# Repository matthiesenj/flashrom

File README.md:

# Flashrom
The main purpose of this project is to implement a flashmemory-based kickstart ROM substitute/switcher for the Commodore Amiga line of computers.
It may also serve as a general-purpose substitute for 27Cx00 compatible JEDEC pinout (EP)ROMs.

It is based around the 29F800 1MB flash memory chip and is very close to the same dimensions as a 40 pin DIP socket, and low profile.

## Disclaimer!
This is a homebrew project - I provide absolutely no warranties or promises about the suitability of this for you or your hardware - if something breaks, it's on yourself!

## Features
- 1MB flash-based programmable (EP)ROM replacement
- About the same size as a 40-pin DIP socket, so fits side by side in Amiga 4000
- Divisible into two or four ROM sections, switchable using regular toggle switch
- Pairable switching for systems using two ROMs, for example Amiga 1200 and 4000
- Slim pins to avoid damage to DIP socket wipes
- Compatibility mode for Amiga 500 rev 3-5, which have two signals swapped in the socket

## Inspiration
There are some other projects out there which are similar to this one, and while I probably can't guarantee that there was no inspirational effects at all from these, all of the electrical design, schematics and PCB layouts in this project were done completely from scratch.

## Compatibility
I've only tested this with Amiga 4000 and Amiga 500, as it's all I have access to, but as the pinout matches 27C400 there's no reason it shouldn't work in other 5V systems using this pinout.
Jumpers provide compatibility with Amiga 500 rev 3 and 5 which has two ROM socket pins swapped (other revs affected?).

## Important!
- Be careful about electrostatic discharge when handling - signals that go to an optional ROM switch have provisions for in-circuit ESD protection
- When using in a 42-pin socket (for 27C160 JEDEC pinout), make sure the board is inserted in socket positions 2-41 - do *not* insert into position 1!
- Make sure not to insert board backwards - the notch marking should match the notch of the socket

## Versatility

## Socket preservation
Dual-wipe DIP sockets will get damaged by inserting a regular pin strip with 0.6 x 0.6 mm square pins into it - or, it's actually when you need to insert a 40 pin DIP chip again, it will cause problems, because the wide pins of the pin strip bends the wipes so they don't spring back properly (a regular DIP chip has about 0.25mm wide pins).

This project is intended to use 1.27mm pin strips with every other pin removed. These can be found with 0.4 x 0.4mm (or slimmer) pins which won't damage the dual-wipe socket.
Because of this, the PCB holes for the pins are smaller to correctly align the strips while being soldered.

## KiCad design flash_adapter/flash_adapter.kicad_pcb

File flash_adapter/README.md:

# TL866CS/A flash adapter for 29Fx00 flashrom project

This PCBA makes it possible to use a TL866 programmer with the TSOP48/SOP44 adapter to program the 29Fx00 flashrom solution.
It's also useful for reading the contents of EPROMs and mask ROMs with a JEDEC pinout matching an Amiga ROM or 27Cx00 EPROM.

The design is very simple, it just reroutes the signals of the TSOP/SOP adapter to match the pinout of mentioned ROMs/EPROMs.
Only a few headers need to be soldered to the board, and the through holes for the main socket are Ø 1.0mm to be able to fit a Textool ZIF socket if so desired.
The 4-wire cable serves to connect the 4 missing signals on the 40-pin DIP interface required for programming (_WE, RY_BY, A18, and _RESET) to the programming adapter

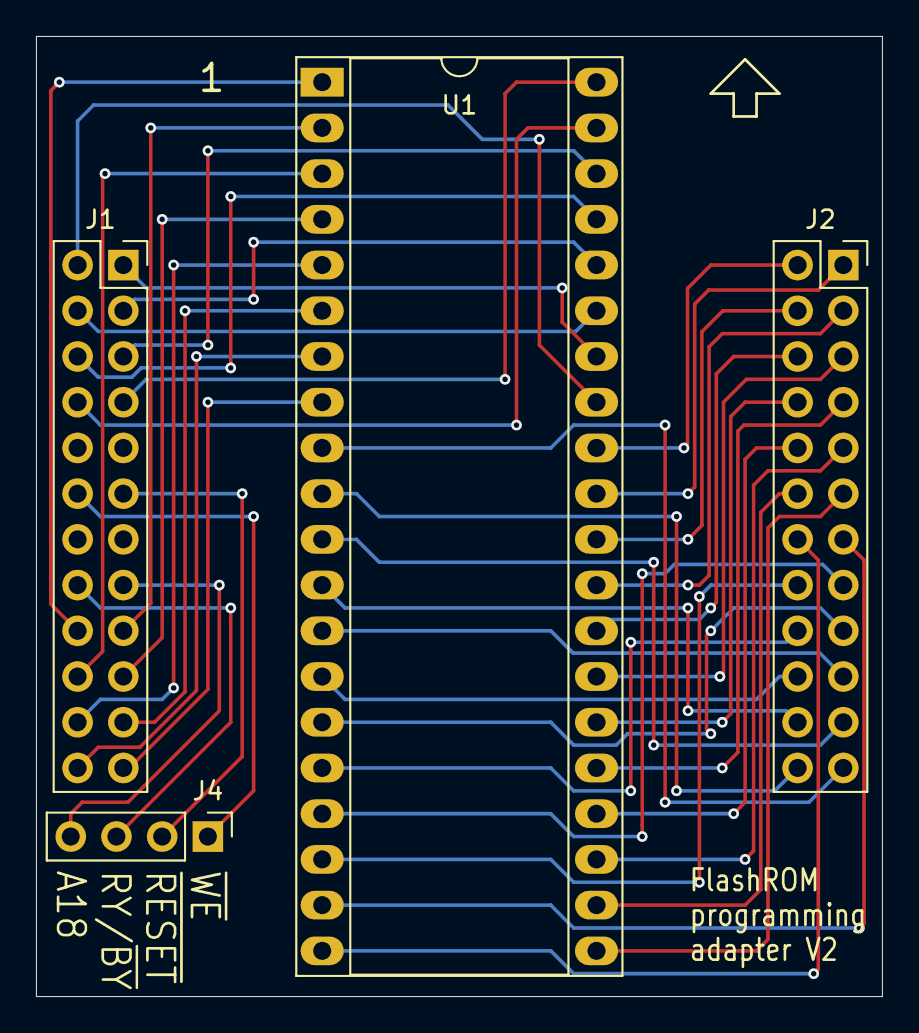
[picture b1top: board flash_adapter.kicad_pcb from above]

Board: 2 copper layers, 47.0 x 53.3 mm, 4 parts (0 on the bottom side), 44 nets.

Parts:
J1, J2: Conn_02x12_Odd_Even; PinSocket_2x12_P2.54mm_Vertical
J4: Conn_01x04_Pin; PinHeader_1x04_P2.54mm_Vertical
U1: Kickstart_Socket_A4000; DIP-40_W15.24mm_Socket_LongPads

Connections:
/A18: J1.15, J4.4
/L1: J1.1, U1.34 (A14)
/L2: J1.2, U1.33 (A15)
/L3: J1.3, U1.36 (A12)
/L4: J1.4, U1.35 (A13)
/L5: J1.5, U1.38 (A10)
/L6: J1.6, U1.37 (A11)
/L7: J1.7, U1.40 (A8)
/L8: J1.8, U1.39 (A9)
/L11: J1.11, J4.2
/L12: J1.12, J4.1
/L16: J1.16, J4.3
/L17: J1.17, U1.2 (A7)
/L18: J1.18, U1.1 (A17)
/L19: J1.19, U1.4 (A5)
/L20: J1.20, U1.3 (A6)
/L21: J1.21, U1.6 (A3)
/L22: J1.22, U1.5 (A4)
/L23: J1.23, U1.8 (A1)
/L24: J1.24, U1.7 (A2)
/R1: J2.1, U1.31 (MODE)
/R2: J2.2, U1.32 (A16)
/R3: J2.3, U1.29 (D15)
/R4: J2.4, U1.30 (GND)
/R5: J2.5, U1.27 (D14)
/R6: J2.6, U1.28 (D7)
/R7: J2.7, U1.25 (D13)
/R8: J2.8, U1.26 (D6)
/R9: J2.9, U1.23 (D12)
/R10: J2.10, U1.24 (D5)
/R11: J2.11, U1.21 (VCC)
/R12: J2.12, U1.22 (D4)
/R13: J2.13, U1.19 (D3)
/R14: J2.14, U1.20 (D11)
/R15: J2.15, U1.17 (D2)
/R16: J2.16, U1.18 (D10)
/R17: J2.17, U1.15 (D1)
/R18: J2.18, U1.16 (D9)
/R19: J2.19, U1.13 (D0)
/R20: J2.20, U1.14 (D8)
/R21: J2.21, U1.11 (GND)
/R22: J2.22, U1.12 (~OE)
/R23: J2.23, U1.9 (A0)
/R24: J2.24, U1.10 (~CS)

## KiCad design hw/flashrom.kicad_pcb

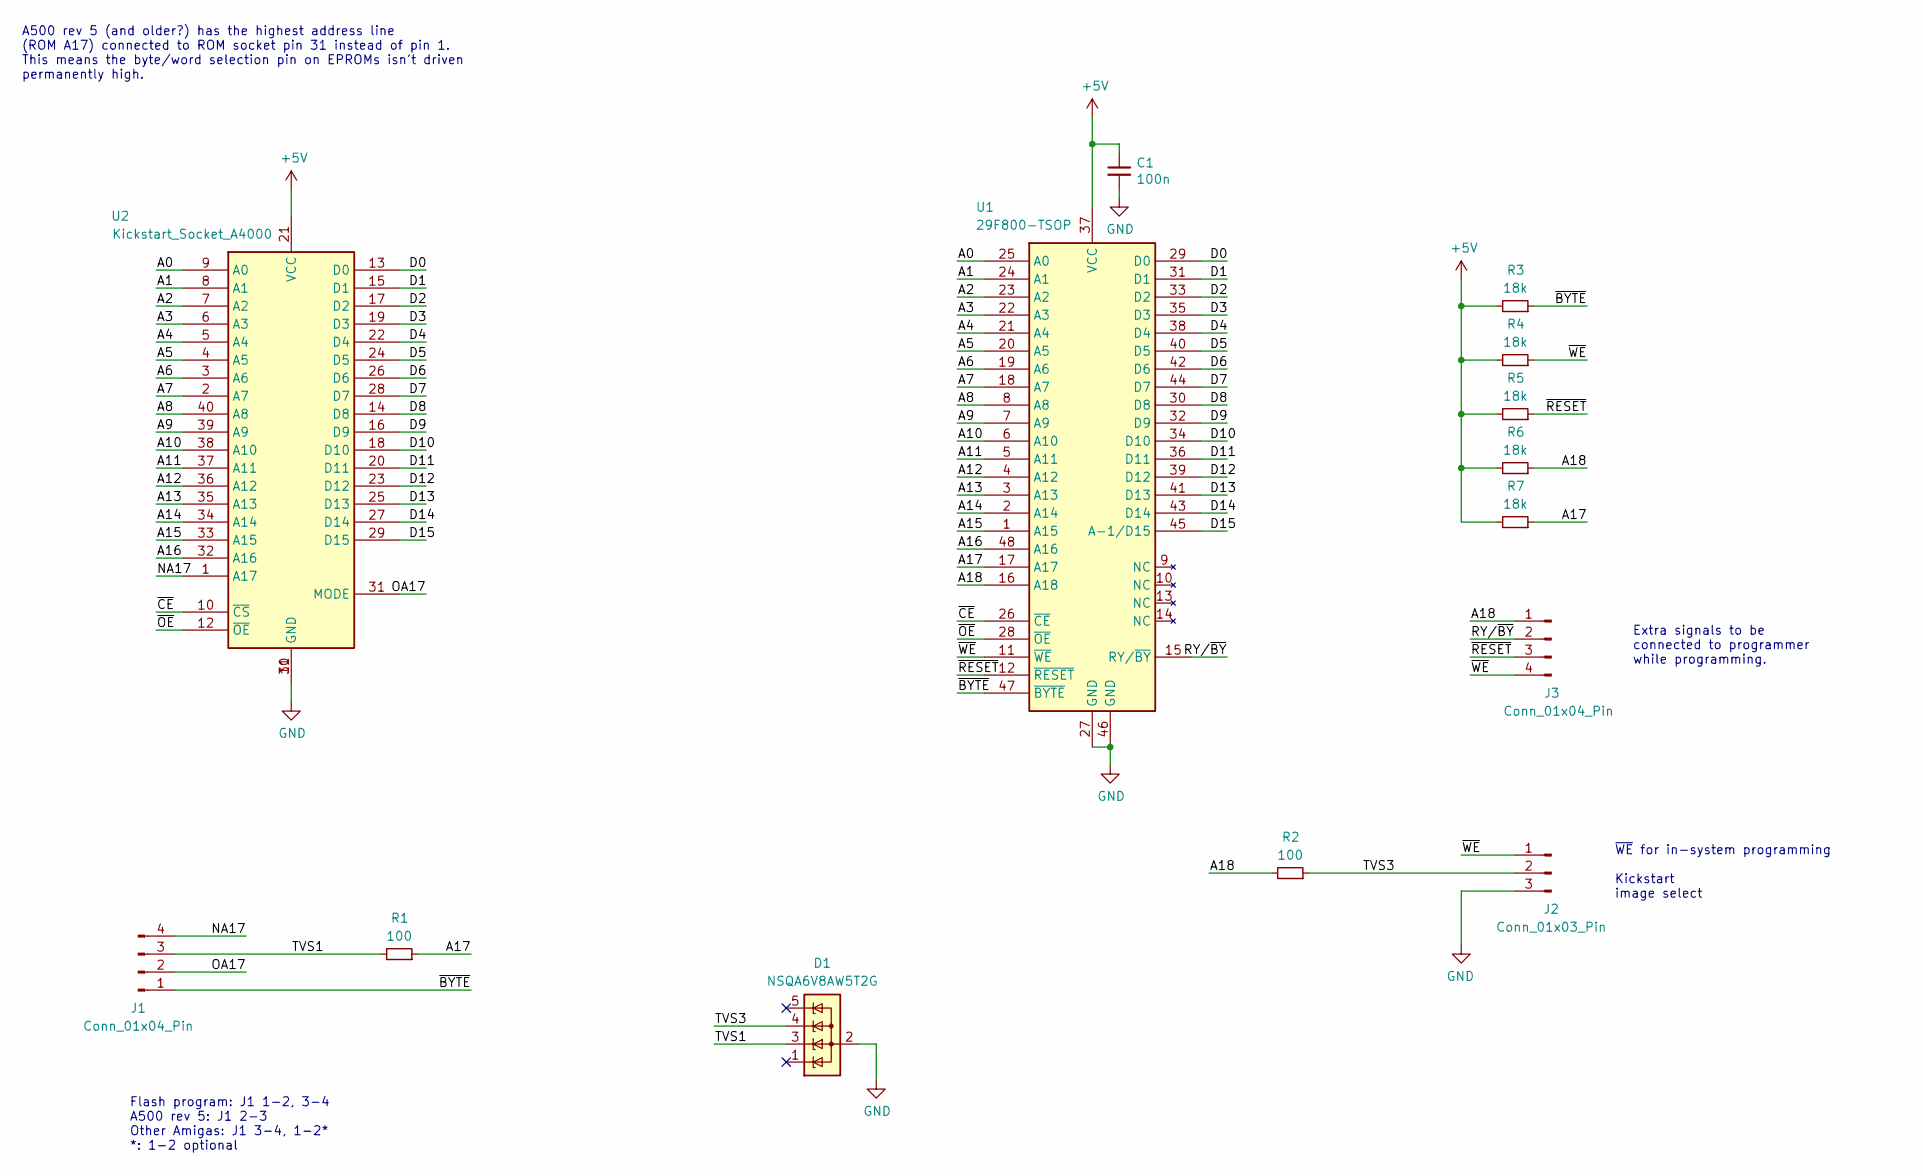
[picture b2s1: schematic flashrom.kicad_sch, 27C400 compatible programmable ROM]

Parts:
C1: 100n; C_0603_1608Metric
D1: NSQA6V8AW5T2G; SOT-353_SC-70-5
J1, J3: Conn_01x04_Pin; Harwin_M20-89004xx_1x04_P2.54mm_Horizontal
J2: Conn_01x03_Pin; Harwin_M20-89003xx_1x03_P2.54mm_Horizontal
R1, R2: 100; R_0603_1608Metric
R3, R4, R5, R6, R7: 18k; R_0603_1608Metric
U1: 29F800-TSOP; TSOP-I-48_18.4x12mm_P0.5mm
U2: Kickstart_Socket_A4000; DIP-40_W15.24mm_Socket

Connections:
+5V: C1.1, R3.2, R4.2, R5.2, R6.2, R7.2, U1.37 (VCC), U2.21 (VCC)
/A0: U1.25 (A0), U2.9 (A0)
/A1: U1.24 (A1), U2.8 (A1)
/A2: U1.23 (A2), U2.7 (A2)
/A3: U1.22 (A3), U2.6 (A3)
/A4: U1.21 (A4), U2.5 (A4)
/A5: U1.20 (A5), U2.4 (A5)
/A6: U1.19 (A6), U2.3 (A6)
/A7: U1.18 (A7), U2.2 (A7)
/A8: U1.8 (A8), U2.40 (A8)
/A9: U1.7 (A9), U2.39 (A9)
/A10: U1.6 (A10), U2.38 (A10)
/A11: U1.5 (A11), U2.37 (A11)
/A12: U1.4 (A12), U2.36 (A12)
/A13: U1.3 (A13), U2.35 (A13)
/A14: U1.2 (A14), U2.34 (A14)
/A15: U1.1 (A15), U2.33 (A15)
/A16: U1.48 (A16), U2.32 (A16)
/A17: R1.1, R7.1, U1.17 (A17)
/A18: J3.1, R2.2, R6.1, U1.16 (A18)
/D0: U1.29 (D0), U2.13 (D0)
/D1: U1.31 (D1), U2.15 (D1)
/D2: U1.33 (D2), U2.17 (D2)
/D3: U1.35 (D3), U2.19 (D3)
/D4: U1.38 (D4), U2.22 (D4)
/D5: U1.40 (D5), U2.24 (D5)
/D6: U1.42 (D6), U2.26 (D6)
/D7: U1.44 (D7), U2.28 (D7)
/D8: U1.30 (D8), U2.14 (D8)
/D9: U1.32 (D9), U2.16 (D9)
/D10: U1.34 (D10), U2.18 (D10)
/D11: U1.36 (D11), U2.20 (D11)
/D12: U1.39 (D12), U2.23 (D12)
/D13: U1.41 (D13), U2.25 (D13)
/D14: U1.43 (D14), U2.27 (D14)
/D15: U1.45 (A-1/D15), U2.29 (D15)
/NA17: J1.4, U2.1 (A17)
/OA17: J1.2, U2.31 (MODE)
/RY/~BY: J3.2, U1.15 (RY/~BY)
/TVS1: D1.3 (K), J1.3, R1.2
/TVS3: D1.4 (K), J2.2, R2.1
/~BYTE: J1.1, R3.1, U1.47 (~BYTE)
/~CE: U1.26 (~CE), U2.10 (~CS)
/~OE: U1.28 (~OE), U2.12 (~OE)
/~RESET: J3.3, R5.1, U1.12 (~RESET)
/~WE: J2.1, J3.4, R4.1, U1.11 (~WE)
GND: C1.2, D1.2 (A), J2.3, U1.27 (GND), U1.46 (GND), U2.11 (GND), U2.30 (GND)

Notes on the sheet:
A500 rev 5 (and older?) has the highest address line (ROM A17) connected to ROM socket pin 31 instead of pin 1. This means the byte/word selection pin on EPROMs isn't driven permanently high.
Flash program: J1 1-2, 3-4 A500 rev 5: J1 2-3 Other Amigas: J1 3-4, 1-2* *: 1-2 optional
Extra signals to be connected to programmer while programming.
~{WE} for in-system programming Kickstart image select

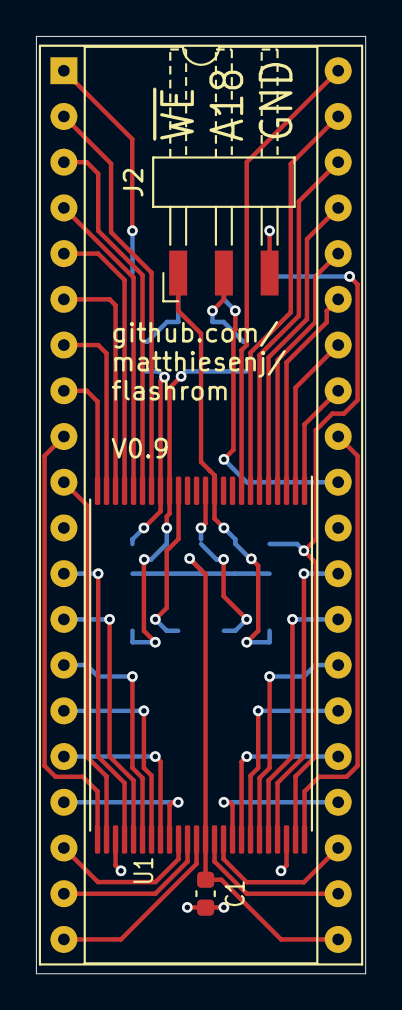
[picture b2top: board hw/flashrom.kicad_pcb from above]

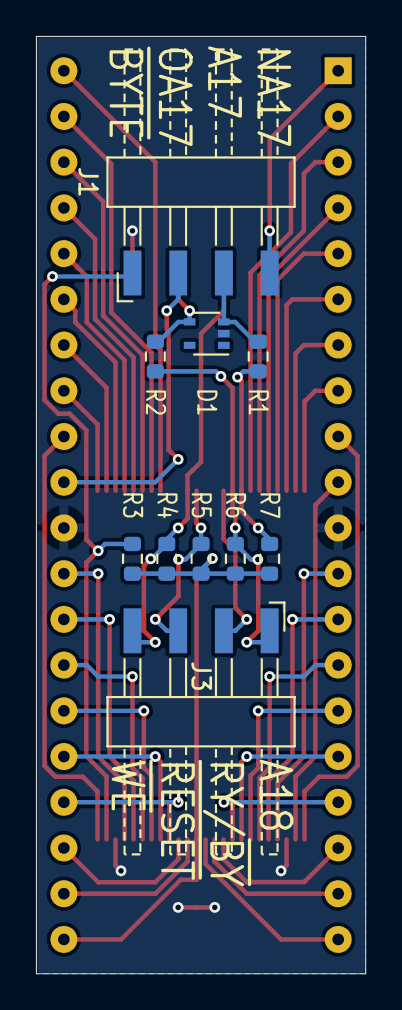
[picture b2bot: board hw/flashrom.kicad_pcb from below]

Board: 2 copper layers, 18.3 x 52.1 mm, 14 parts (10 on the bottom side), 47 nets.

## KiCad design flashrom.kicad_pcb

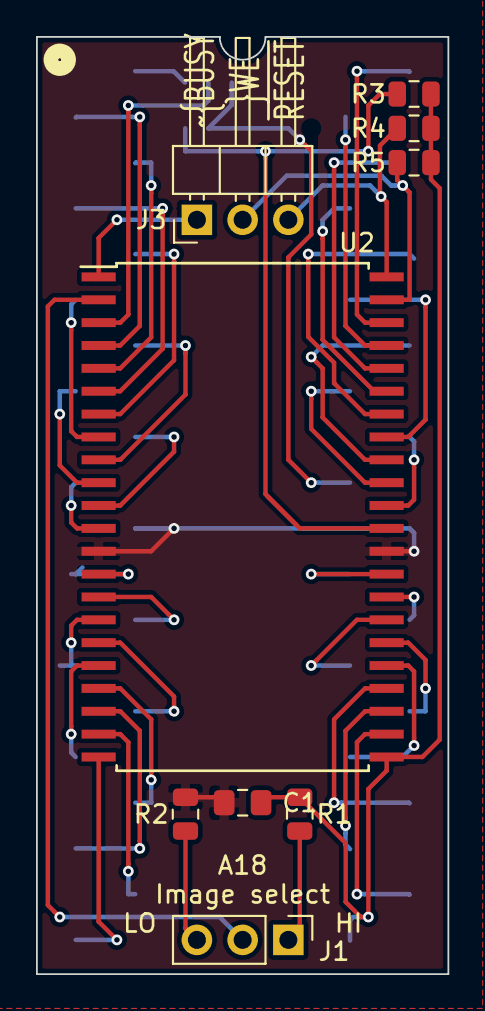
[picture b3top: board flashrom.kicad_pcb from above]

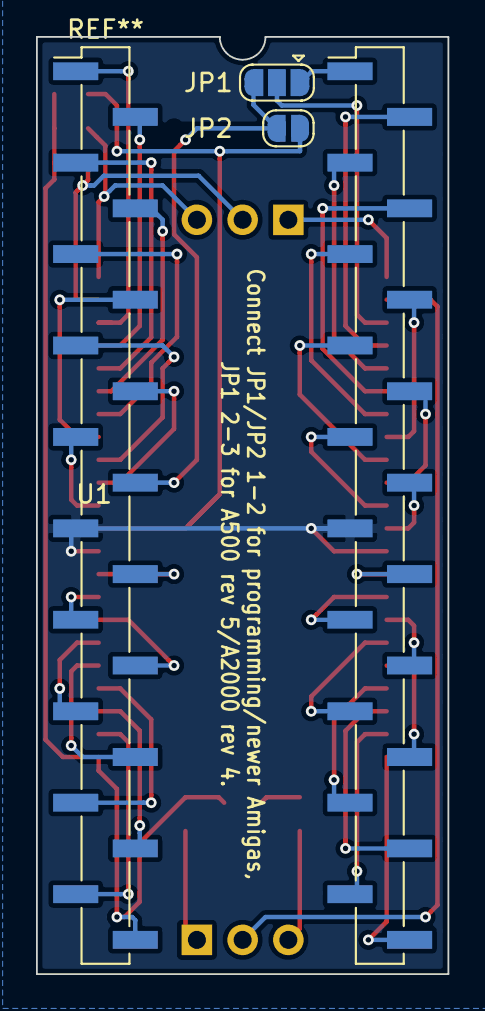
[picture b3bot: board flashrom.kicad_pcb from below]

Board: 2 copper layers, 22.9 x 52.1 mm, 12 parts (3 on the bottom side), 47 nets.

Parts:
C1: 100n; C_0805_2012Metric_Pad1.15x1.40mm_HandSolder
J1: Conn_01x03_Male; PinHeader_1x03_P2.54mm_Vertical
J3: Conn_01x03_Male; PinHeader_1x03_P2.54mm_Horizontal
JP1: SolderJumper_3_Bridged12; SolderJumper-3_P1.3mm_Open_RoundedPad1.0x1.5mm
JP2: SolderJumper_2_Bridged; SolderJumper-2_P1.3mm_Open_RoundedPad1.0x1.5mm
R1, R2, R3, R4, R5: 10k; R_0805_2012Metric
U1: Kickstart_Socket_A4000; DIP-40_W15.24mm_SMDHeader
U2: 29F800; PSOP-44_16.9x27.17mm_P1.27mm

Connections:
+5V: C1.1, R1.1, R3.1, R4.1, R5.1, U1.21, U2.23
/A0: U1.9, U2.11
/A1: U1.8, U2.10
/A2: U1.7, U2.9
/A3: U1.6, U2.8
/A4: U1.5, U2.7
/A5: U1.4, U2.6
/A6: U1.3, U2.5
/A7: U1.2, U2.4
/A8: U1.40, U2.42
/A9: U1.39, U2.41
/A10: U1.38, U2.40
/A11: U1.37, U2.39
/A12: U1.36, U2.38
/A13: U1.35, U2.37
/A14: U1.34, U2.36
/A15: U1.33, U2.35
/A16: U1.32, U2.34
/A17: JP1.2, U2.3
/A18: J1.2, U2.2
/D0: U1.13, U2.15
/D1: U1.15, U2.17
/D2: U1.17, U2.19
/D3: U1.19, U2.21
/D4: U1.22, U2.24
/D5: U1.24, U2.26
/D6: U1.26, U2.28
/D7: U1.28, U2.30
/D8: U1.14, U2.16
/D9: U1.16, U2.18
/D10: U1.18, U2.20
/D11: U1.20, U2.22
/D12: U1.23, U2.25
/D13: U1.25, U2.27
/D14: U1.27, U2.29
/D15: U1.29, U2.31
/NA17: JP1.1, U1.1
/OA17: JP1.3, JP2.2, U1.31
/~CE: U1.10, U2.12
/~OE: U1.12, U2.14
/~RESET: J3.3, R4.2, U2.44
/~WE: J3.2, R5.2, U2.43
GND: C1.2, R2.2, U1.11, U1.30, U2.13, U2.32
unnamed: J1.1, R1.2
unnamed: J1.3, R2.1
unnamed: J3.1, U2.1
unnamed: JP2.1, R3.2, U2.33

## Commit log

2020-11-02 Create LICENSE
2020-11-02 move kicad project to hw dir
2020-11-02 add 29F800-TSOP
2020-11-02 add gitignore
2024-12-13 convert project to kicad 7 format
2024-12-18 add a1200 kickstart socket symbol
2024-12-18 switch flash to tsop, add tvs, and route pcb
2024-12-18 ignore *.bak files
2024-12-19 initial commit of tl866 flash adapter files
2024-12-22 finish routing
2024-12-23 change pin 1 of j2 to /WE to support a wire for in-system programming
2024-12-23 move c1 to f.cu for lesser inductance
2024-12-23 update Ux footprints to match library
2024-12-23 set gerber and drill output options
2024-12-25 increase silkscreen line width; manufacturability
2024-12-25 change product text to github repo url
2024-12-28 add J4 silkscreen pin descriptions
2025-01-12 increase dip 40 socket hole size in order to allow use of textool socket
2025-01-12 update schematic legend
2025-01-14 narrow pcb to 18.3mm width to fit a4000d
2025-01-14 switch j3 footprint to horizontal pin header
2025-01-15 switch j1 and j2 footprints to smd horizontal header
2025-01-15 use unfilled rectangle for pin header pin 1 silkscreen so not to cover up pin functions
2025-01-15 add readme for flash adapter
2025-01-25 update graphics
2025-01-25 update text
2025-01-25 main readme work
2025-01-26 increase pull-ups to 18k, the value actually used in the protos
2025-01-26 relocate header for non-socket signals to next to socket to avoid through holes under textool
2025-01-26 update readme's
2025-01-26 add pictures and update picture links
